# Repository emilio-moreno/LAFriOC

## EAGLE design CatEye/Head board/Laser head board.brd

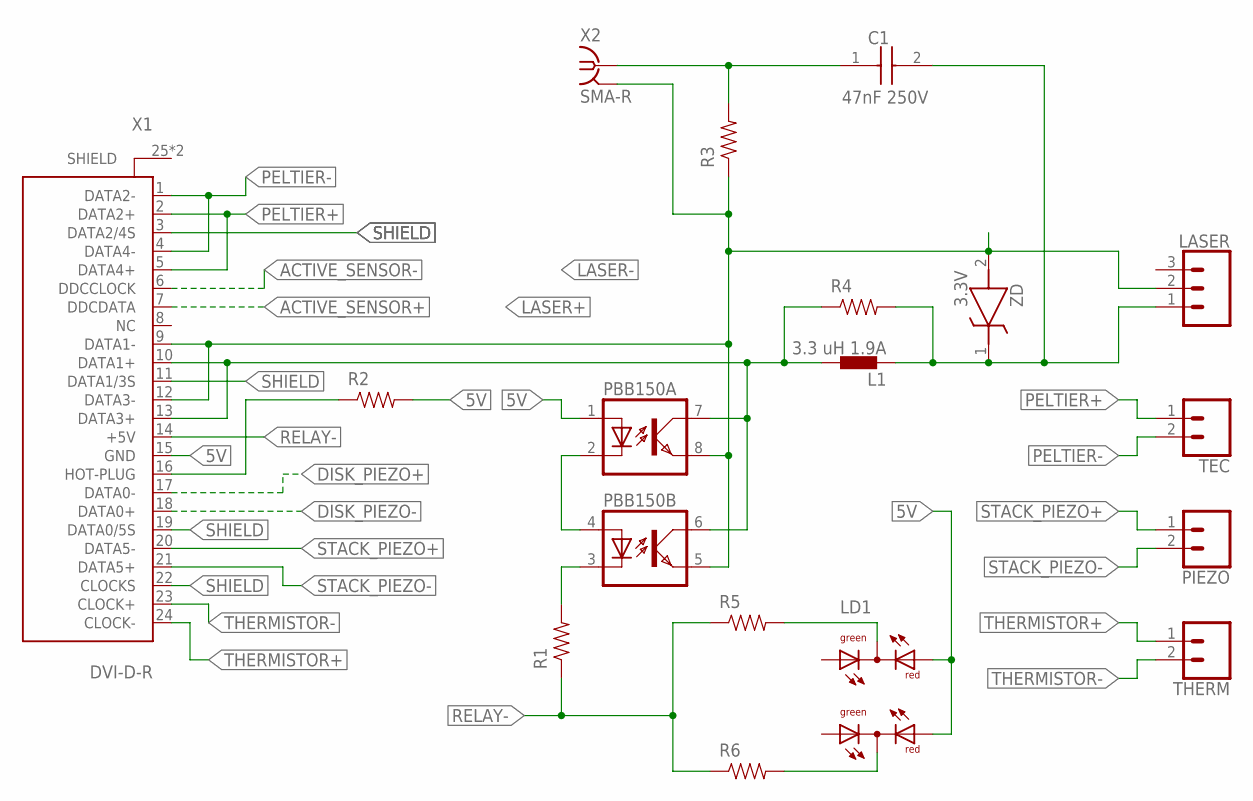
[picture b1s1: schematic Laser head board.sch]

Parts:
C1: 47nF 250V; OCR_CAPC3216X180N
L1: 3.3 uH 1.9A; OCR_INDC7070
LASER: OCR_CONN_03; OCR_MOLEX-1X3_LOCK
LD1: OCR_WP130WCP/2EGW
PBB150: OCR_PBB150; OCR_DIL08
PIEZO: OCR_CONN_02; OCR_MOLEX-1X2_LOCK
R1: 390R; OCR_0805
R2: 4k99; OCR_0805
R3: 10k; OCR_0805
R4: 43R; OCR_0805
R5, R6: 499R; OCR_0805
TEC: OCR_CONN_02; OCR_MOLEX-1X2_LOCK
THERM: OCR_CONN_02; OCR_MOLEX-1X2_LOCK
X1: DVI-D-R; OCR_DVI-D-R
X2: SMA-R; OCR_SMA_0732512201
ZD: 3.3V; OCR_SOD3716X135N

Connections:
5V: LD1.R1, LD1.R2, PBB150.1 (A), R2.2, X1.15 (GND)
ACTIVE_SENSOR+: X1.7 (DDCDATA)
ACTIVE_SENSOR-: X1.6 (DDCCLOCK)
DISK_PIEZO+: X1.17 (DATA0-)
DISK_PIEZO-: X1.18 (DATA0+)
INTERLOCK+: R2.1, X1.16 (HOT-PLUG)
LASER+: L1.2, PBB150.6 (COL), PBB150.7 (COL), R4.1, X1.10 (DATA1+), X1.13 (DATA3+)
LASER-: LASER.2, PBB150.5 (EMIT), PBB150.8 (EMIT), R3.1, X1.9 (DATA1-), X1.12 (DATA3-), X2.2, X2.3 (2), X2.4 (2), X2.5 (2), ZD.2 (A)
unnamed: LD1.GND1, R5.2
unnamed: C1.1, R3.2, X2.1
unnamed: LD1.GND2, R6.2
unnamed: PBB150.2 (C), PBB150.4 (A)
unnamed: PBB150.3 (C), R1.2
unnamed: C1.2, L1.1, LASER.1, R4.2, ZD.1 (K)
PELTIER+: TEC.1, X1.2 (DATA2+), X1.5 (DATA4+)
PELTIER-: TEC.2, X1.1 (DATA2-), X1.4 (DATA4-)
RELAY-: R1.1, R5.1, R6.1, X1.14 (+5V)
SHIELD: X1.3 (DATA2/4S), X1.11 (DATA1/3S), X1.19 (DATA0/5S), X1.22 (CLOCKS), X1.25 (SHIELD), X1.26 (SHIELD)
STACK_PIEZO+: PIEZO.1, X1.20 (DATA5-)
STACK_PIEZO-: PIEZO.2, X1.21 (DATA5+)
THERMISTOR+: THERM.1, X1.24 (CLOCK-)
THERMISTOR-: THERM.2, X1.23 (CLOCK+)

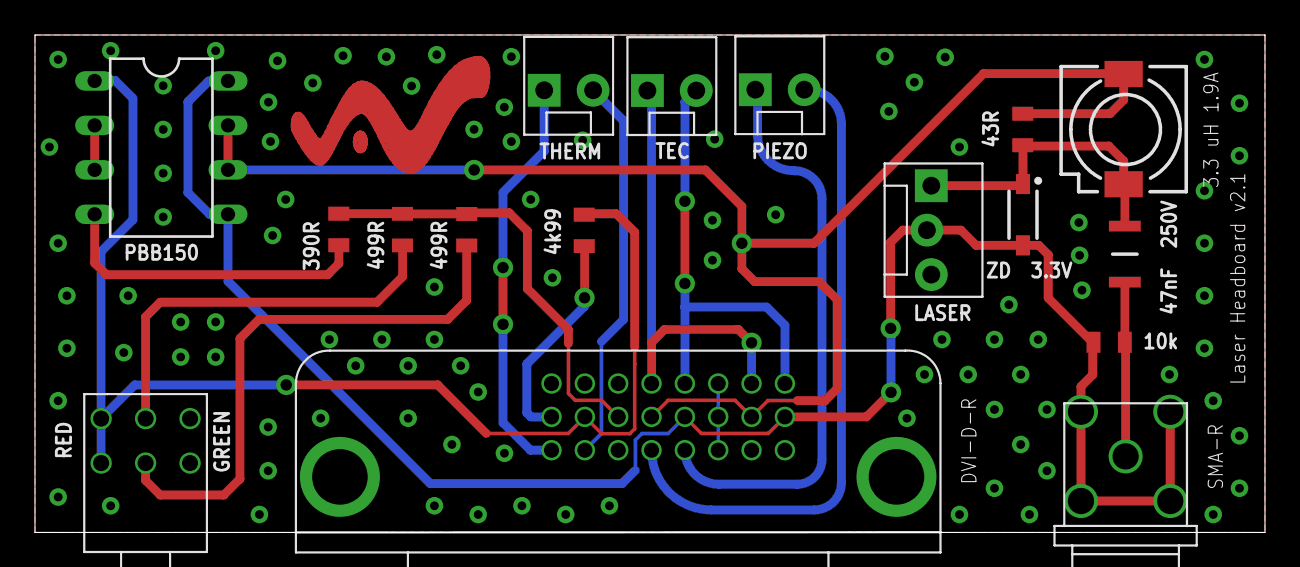
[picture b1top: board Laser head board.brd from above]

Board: 2 copper layers, 70.3 x 28.4 mm, 18 parts (1 on the bottom side), 18 nets.

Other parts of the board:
U$2: LANMAC_2.0_COPPER

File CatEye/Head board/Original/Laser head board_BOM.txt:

Qty Value       Device              Package        Parts             Description                                                                                                     AVAILABILITY DESCRIPTION                                                                             HEIGHT MANUFACTURER_NAME MANUFACTURER_PART_NUMBER MF  MOUSER_PART_NUMBER MP                  PACKAGE         PRICE   
3               CONN_02             MOLEX-1X2_LOCK PIEZO, TEC, THERM Multi connection point. Often used as Generic Header-pin footprint for 0.1 inch spaced/style header connections                                                                                                                                                                                                                           
1               CONN_03             MOLEX-1X3_LOCK LASER             Multi connection point. Often used as Generic Header-pin footprint for 0.1 inch spaced/style header connections                                                                                                                                                                                                                           
1               PBB150              DIL08          PBB150            Mfr: IXYS Integrated Circuits                                                                                                                                                                                                                                                                                                             
1               WP130WCP/2EGW       WP130WCP/2EGW  LD1               Kingbright LED                                                                                                                                                                                                                                                                                                                            
1   10k         RESISTOR            0805           R3                0.75Ω resistor                                                                                                                                                                                                                                                                                                                            
1   3.3 uH 1.9A SLF7032T            INDC7070       L1                Fixed Inductors 100uH 0.6A                                                                                      Good          Inductor Power Shielded Wirewound 100uH 20% 100KHz Ferrite 650mA 300mOhm DCR T/R                                                         TDK                    SLF7045T-101MR50-PF Nonstandard TDK 0.56 USD
1   3.3V        MMSZ3V3T1G          SOD3716X135N   ZD                500 mW 3.3 V 5% ZenerDiodeVoltage Regulator                                                                                  500 mW 3.3 V 5% ZenerDiodeVoltage Regulator                                             1.35mm ON Semiconductor  MMSZ3V3T1G                   863-MMSZ3V3T1G                                                 
1   390R        RESISTOR            0805           R1                0.75Ω resistor                                                                                                                                                                                                                                                                                                                            
1   43R         RESISTOR            0805           R4                0.75Ω resistor                                                                                                                                                                                                                                                                                                                            
1   47nF 250V   C3216X7R2E473K160AA CAPC3216X180N  C1                TDK C3216 C 47nF Ceramic Multilayer Capacitor, 250 V dc, +125C, X7R Dielectric, 10% SMD                                      TDK C3216 C 47nF Ceramic Multilayer Capacitor, 250 V dc, +125C, X7R Dielectric, 10% SMD 1.8mm  TDK               C3216X7R2E473K160AA          810-C3216X7R2E473K                                             
2   499R        RESISTOR            0805           R5, R6            0.75Ω resistor                                                                                                                                                                                                                                                                                                                            
1   4k99        RESISTOR            0805           R2                0.75Ω resistor                                                                                                                                                                                                                                                                                                                            
1   DVI-D-R     DVI-D-R_74320       DVI-D-R        X1                74320-9004                                                                                                                                                                                                                                                                                                                                
1   SMA-R       SMA-R/A             SMA_0732512201 X2                SMA CONNECTOR

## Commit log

2025-03-10 PixelFly first measurements
2025-03-21 Exposure vs power for saturation
2025-03-21 html
2025-03-26 Spectroscopy
2025-03-27 Saturation update
2025-04-02 Hyperfine structure
2025-04-03 More examples
2025-04-03 Histogram counts
2025-04-04 Rescaling
2025-04-11 Rb oven housing
2025-04-11 Rb oven examples
2025-04-25 Fine structure / Zeeman Effect
2025-04-28 Selection rules
2025-04-29 Rb oven deisgn updated
2025-05-09 Rb PEEK
2025-05-09 Two windows
2025-05-12 Rubidium HFS
2025-05-16 MS-1L Shield
2025-05-16 Rb Oven Full Design
2025-05-19 Updated PEEK design
2025-05-19 Added breadboard support
2025-05-19 1/4" Heaters
2025-06-05 Watlow
2025-06-13 Adjusted PEEK cover to fit bigger copper housing
2025-06-20 PEEK 20/06/25
2025-06-26 Head board
2025-06-27 Threshold current and modes
2025-07-03 Headboard STEP files
2025-07-03 Updated EAGLE files
2025-07-04 LAFriOC logo
2025-07-04 Original laser head board
2025-07-04 STEP files
2025-07-04 More STEPs
2025-07-28 Spectroscopy analysis
    Added peak and baseline finding.
2025-07-31 Added 3D Models for cateye, thermistor holes to Rb oven
2025-08-02 MOGLabs PCB pictures
2025-08-14 PEEK dimensions
2025-09-05 Cateye
2025-09-19 Rb oven pack&go
2025-09-26 MOT Vacuum System
2025-09-26 MOT Posts
2025-10-01 Cateye drawings
2025-10-09 ICFO
